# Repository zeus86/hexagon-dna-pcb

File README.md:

# Hexagon-DNA - PCB and gerber files

These are the gerber and Kicad-Files for the Hexagon-DNA-Lamp. The 3D-Model as well as some pictures can be found on my [printables-project](https://www.printables.com/model/1434750-hexagon-dna-lamp).  

As the PCB is within the 10x10cm-boundaries, you can have them manufactured very cheaply from your favorite PCB-manufacturer. You can get them for around 5$ (+shipping), which is supercheap, and the quality is superb.  
However, someone at PCBWay has found my project on printables and contacted me if I was interested in trying out their quality also. As I needed some more PCBs anyways, and I happily aggreed.  
I mean what can I say: It is absolutely impressive how far hobby-level pcb-manufacturing has come. All PCBs, be it from PCBWay other manufacturers were absolutely immmaculate and much nicer as what you get inside of commercial products. For that price ordering PCBs have become as easy as it can get, and you get absolutely superb quality.  

Some closeup-images can be found in [here](/img). The white PCBs are the corrected version which were manufactured by PCBWay. They have the power-pinouts now mirrored, so that JST-XH-Plugs fit the right way around. All of them function perfectly fine, and I like the white as much as the purple ones. I really should try out some other colors next time :) . 

## Assembly

Assembly instructions are in the [printables-project](https://www.printables.com/model/1434750).

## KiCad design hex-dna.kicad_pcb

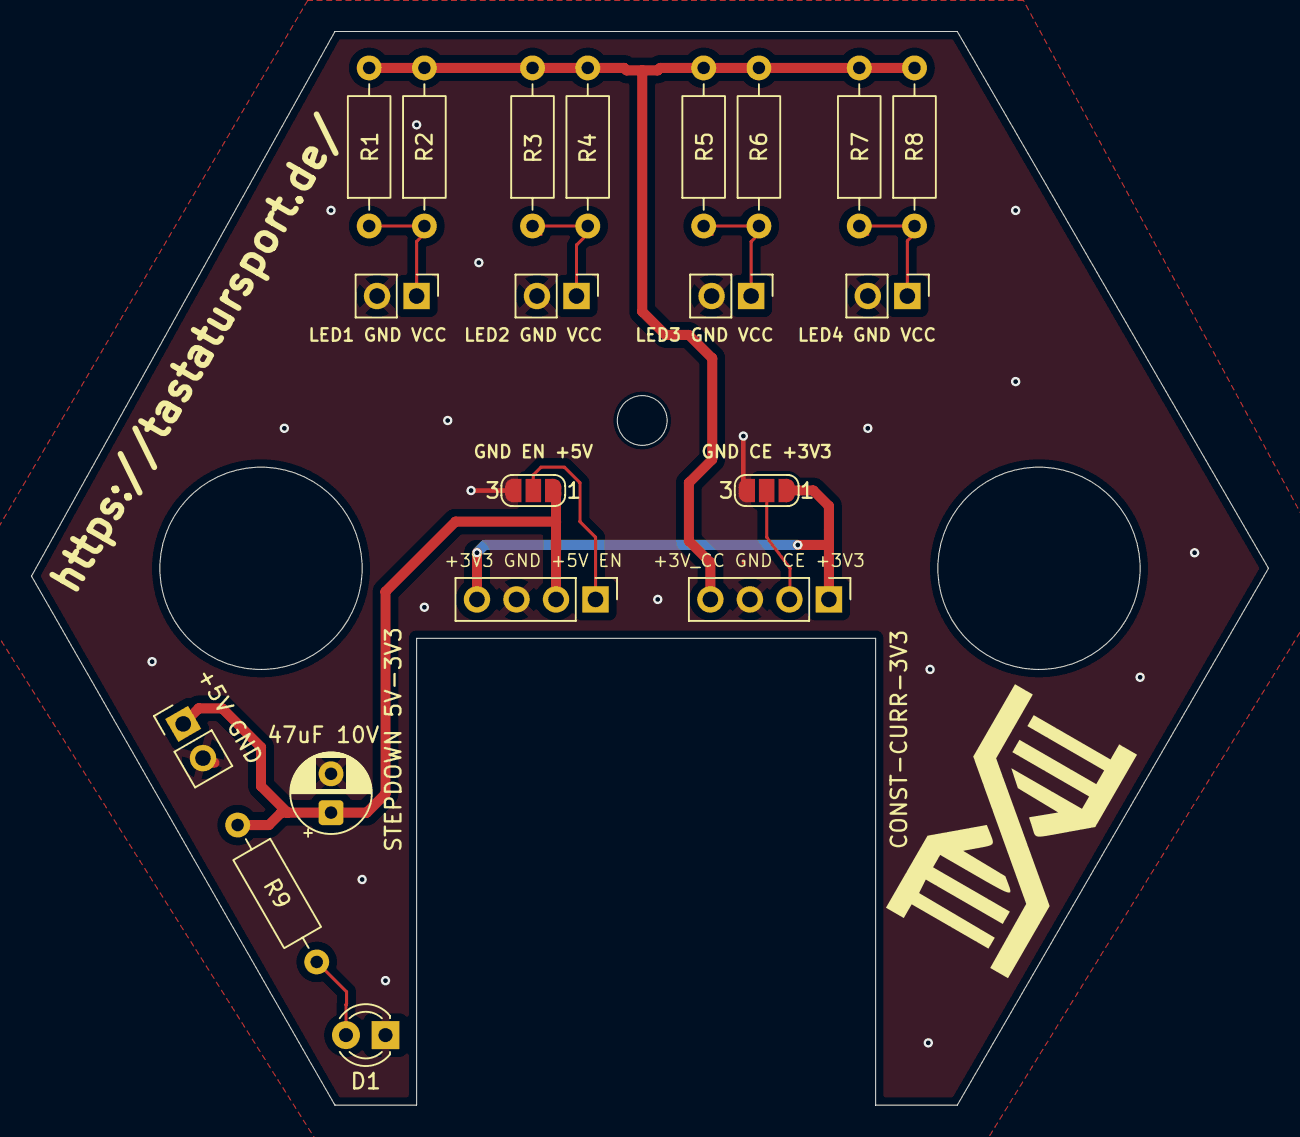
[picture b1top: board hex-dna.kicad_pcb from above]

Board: 2 copper layers, 79.5 x 69.0 mm, 21 parts (0 on the bottom side), 11 nets.

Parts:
+3V3 GND +5V EN: STEPDOWN 5V-3V3; PinHeader_1x04_P2.54mm_Vertical
+3V_CC GND CE +3V3: CONST-CURR-3V3; PinHeader_1x04_P2.54mm_Vertical
C1: 47uF 10V; CP_Radial_D5.0mm_P2.50mm
D1: LED; LED_D3.0mm
H1: MountingHole; MountingHole_3.2mm_M3
J1: +5V GND; PinHeader_1x02_P2.54mm_Vertical
J2: LED1 GND VCC; PinHeader_1x02_P2.54mm_Vertical
J3: LED2 GND VCC; PinHeader_1x02_P2.54mm_Vertical
J4: LED3 GND VCC; PinHeader_1x02_P2.54mm_Vertical
J7: LED4 GND VCC; PinHeader_1x02_P2.54mm_Vertical
JP1: GND EN +5V; SolderJumper-3_P1.3mm_Open_RoundedPad1.0x1.5mm_NumberLabels
JP2: GND CE +3V3; SolderJumper-3_P1.3mm_Open_RoundedPad1.0x1.5mm_NumberLabels
R1, R2, R3, R4, R5, R6, R7, R8, R9: R; R_Axial_DIN0207_L6.3mm_D2.5mm_P10.16mm_Horizontal

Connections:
+3V3: +3V3 GND +5V EN.4, +3V_CC GND CE +3V3.1, JP2.1 (A)
+3V_const: +3V_CC GND CE +3V3.4, R1.2, R2.2, R3.2, R4.2, R5.2, R6.2, R7.2, R8.2
+5V: +3V3 GND +5V EN.2, C1.1, J1.1, JP1.1 (A), R9.1
GND: +3V3 GND +5V EN.3, +3V_CC GND CE +3V3.3, C1.2, D1.1 (K), J1.2, J2.2, J3.2, J4.2, J7.2, JP1.3 (B), JP2.3 (B)
unnamed: D1.2 (A), R9.2
unnamed: J2.1, R1.1, R2.1
unnamed: J3.1, R3.1, R4.1
unnamed: J4.1, R5.1, R6.1
unnamed: +3V_CC GND CE +3V3.2, JP2.2 (C)
unnamed: +3V3 GND +5V EN.1, JP1.2 (C)
unnamed: J7.1, R7.1, R8.1

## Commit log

2025-10-05 gitignore
2025-10-05 added main project files
2025-10-05 added image, edited readme
2025-10-05 typo
2025-10-05 added image of assembled pcb
2025-10-05 crop
2025-10-05 schematics
2025-10-05 used correct link
2025-11-21 new gerber files
2025-11-21 reordered images, added V2 from pcbway
2025-11-21 renamed images
2025-11-24 README
2025-11-24 image reodering
2025-11-24 fixed minor silkscreen error
